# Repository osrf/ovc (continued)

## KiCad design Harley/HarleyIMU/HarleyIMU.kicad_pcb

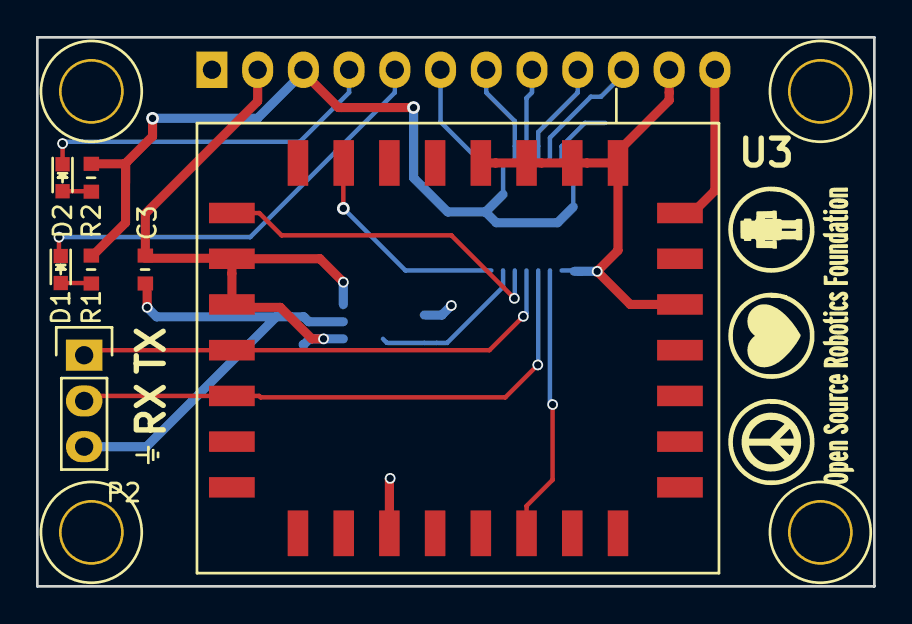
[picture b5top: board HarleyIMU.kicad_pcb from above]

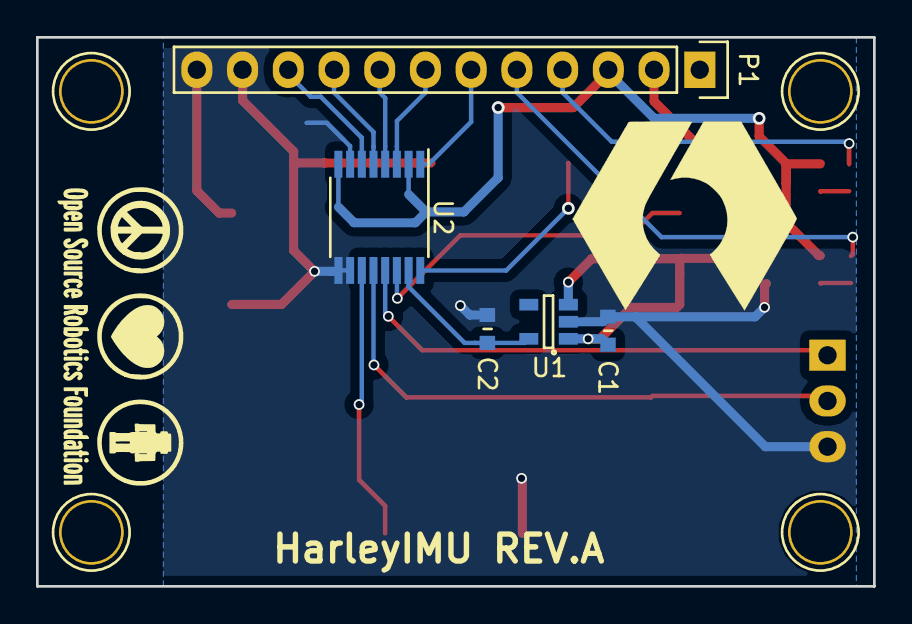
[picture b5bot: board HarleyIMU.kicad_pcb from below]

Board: 2 copper layers, 46.5 x 30.5 mm, 12 parts (5 on the bottom side), 18 nets.

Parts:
C1, C2: 1u; C_0603
C3: 100n; C_0603
D1: GREEN; LED_0603
D2: RED; LED_0603
P1: CONN_01X12; Pin_Header_Straight_1x12
P2: CONN_01X03; Pin_Header_Straight_1x03
R1, R2: 200; R_0603
U1: MIC5365-3.0YC5-TR; SOT-23-5
U2: TXB0106PWR; TSSOP-16_4.4x5mm_Pitch0.65mm
U3: VN-100; QFN-30_100milpitch

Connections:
3V: C2.1, U1.5, U2.15
+2V5: P1.3, R1.1, R2.1, U2.2, U2.8
+3V3: C1.1, C3.1, P1.2, U1.1, U1.3, U3.10, U3.11
FPGA_Signal1: D2.1, P1.4
FPGA_Signal2: D1.1, P1.5
GND: C1.2, C2.2, C3.2, P1.11, P1.12, P2.3, U1.2, U2.7, U2.9, U2.10, U3.1, U3.2, U3.3, U3.4, U3.18, U3.28, U3.30
IMU_RST#: U2.11, U3.21
IMU_RST#_2V5: P1.10, U2.6
IMU_RX: P2.2, U2.12, U3.13
IMU_RX_2V5: P1.9, U2.5
IMU_SYNC_OUT: U2.14, U3.9
IMU_SYNC_OUT_2V5: P1.7, U2.3
IMU_TARE: U2.16, U3.7
IMU_TARE_2V5: P1.6, U2.1
IMU_TX: P2.1, U2.13, U3.12
IMU_TX_2V5: P1.8, U2.4
unnamed: D1.2, R1.2
unnamed: D2.2, R2.2
